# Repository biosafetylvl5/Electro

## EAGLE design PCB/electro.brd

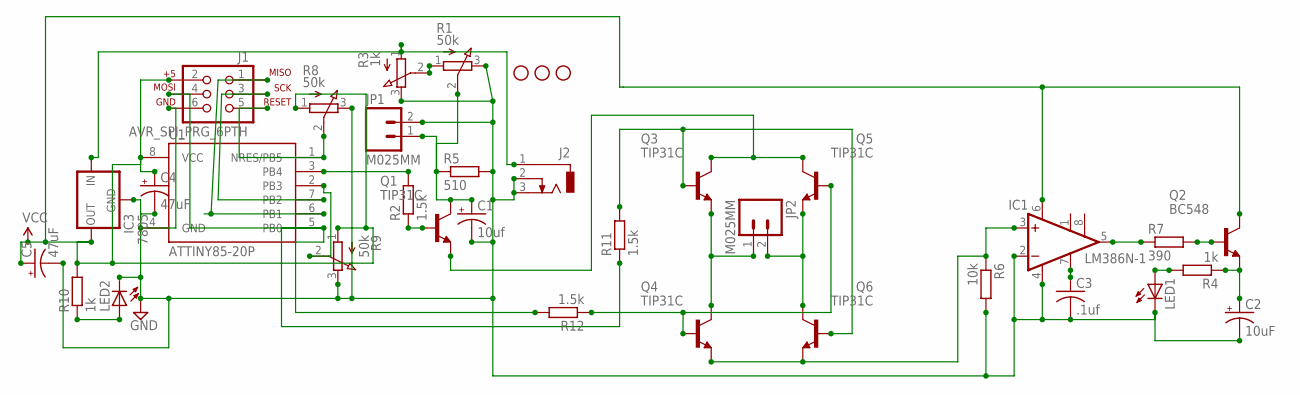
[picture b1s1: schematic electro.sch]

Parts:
C1: 10uf; E2,5-6E
C2: 10uF; E2,5-6E
C3: .1uf; C025-025X050
C4, C5: 47uF; E2,5-6
IC1: LM386N-1; DIL08
IC3: 7805; 78XXL
J1: AVR_SPI_PRG_6PTH; 2X3
J2: DCJ0303
JP1, JP2: M025MM; SCREWTERMINAL-5MM-2
LED1, LED2: LED_ELD260; LED_LD260
Q1, Q3, Q4, Q5, Q6: TIP31C; TO220
Q2: BC548; TO92-EBC
R1, R8, R9: 50k; 3RP/1610N
R2, R11, R12: 1.5k; 0207/10
R3: 1k; 3RP/1610N
R4, R10: 1k; 0207/10
R5: 510; 0207/10
R6: 10k; 0207/10
R7: 390; 0207/10
STANDOFF2, STANDOFF3, STANDOFF4: STAND-OFF
U1: ATTINY85-20P; PDIP08_300MIL

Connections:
GND: C1.-, C2.-, C3.2, C4.-, C5.-, IC1.2 (-IN), IC1.4 (GND), IC3.GND, J1.6, J2.2, J2.3, JP1.2, LED1.K (C), LED2.K (C), R1.3 (E), R3.3 (E), R5.2, R6.2, R8.3 (E), R9.3 (E), U1.4 (GND)
unnamed: R1.1 (A), R3.2 (S)
unnamed: R9.2 (S), U1.2 (PB3)
unnamed: C2.+, Q2.E, R4.1
unnamed: R2.2, U1.3 (PB4)
unnamed: Q1.1 (B), R2.1
unnamed: J1.5, R8.2 (S), U1.1 (NRES/PB5)
unnamed: C1.+, JP1.1, Q1.2 (C), R1.2 (S), R5.1
unnamed: Q3.1 (B), Q6.1 (B), R11.2
unnamed: J1.1, U1.6 (PB1)
unnamed: JP2.1, Q3.3 (E), Q4.2 (C)
unnamed: IC1.5 (OUT), R7.1
unnamed: JP2.2, Q5.3 (E), Q6.2 (C)
unnamed: C3.1, IC1.7 (BYPASS)
unnamed: Q2.B, R7.2
unnamed: J1.3, U1.7 (PB2)
unnamed: Q4.1 (B), Q5.1 (B), R12.1
unnamed: Q1.3 (E), Q3.2 (C), Q5.2 (C)
unnamed: J1.4, R11.1, R12.2, U1.5 (PB0)
unnamed: LED1.A, R4.2
unnamed: LED2.A, R10.1
unnamed: IC1.3 (+IN), Q4.3 (E), Q6.3 (E), R6.1

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
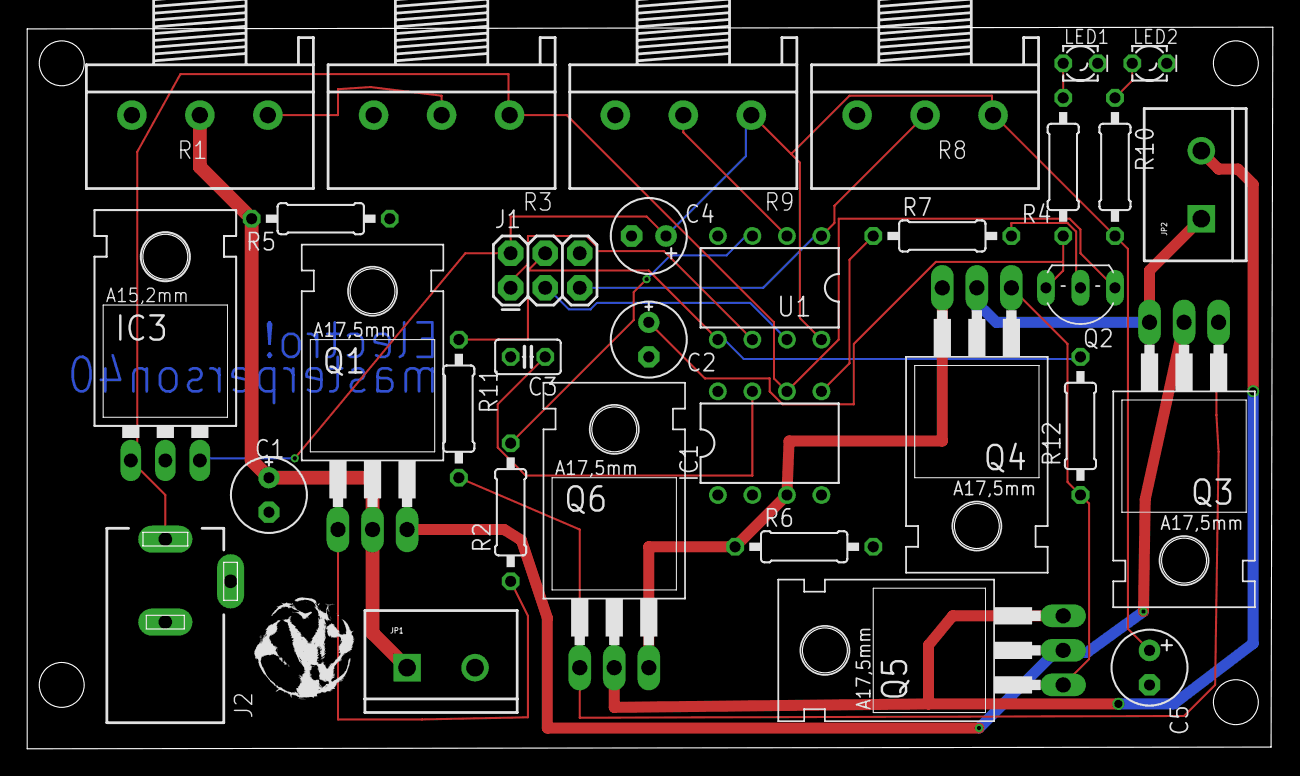
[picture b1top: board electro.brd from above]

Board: 2 copper layers, 91.6 x 53.1 mm, 36 parts (0 on the bottom side), 24 nets.

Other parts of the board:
STANDOFF1: STAND-OFF

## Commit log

2015-04-10 :lollipop: Added .gitattributes

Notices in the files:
parts and their libraries:
SparkFun-Connectors: Licensing: Creative Commons ShareAlike 4.0 International - https://creativecommons.org/licenses/by-sa/4.0
